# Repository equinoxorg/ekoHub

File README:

Hardware:
Contains all PCB designs and hardware related stuff

Other Folders will come soon

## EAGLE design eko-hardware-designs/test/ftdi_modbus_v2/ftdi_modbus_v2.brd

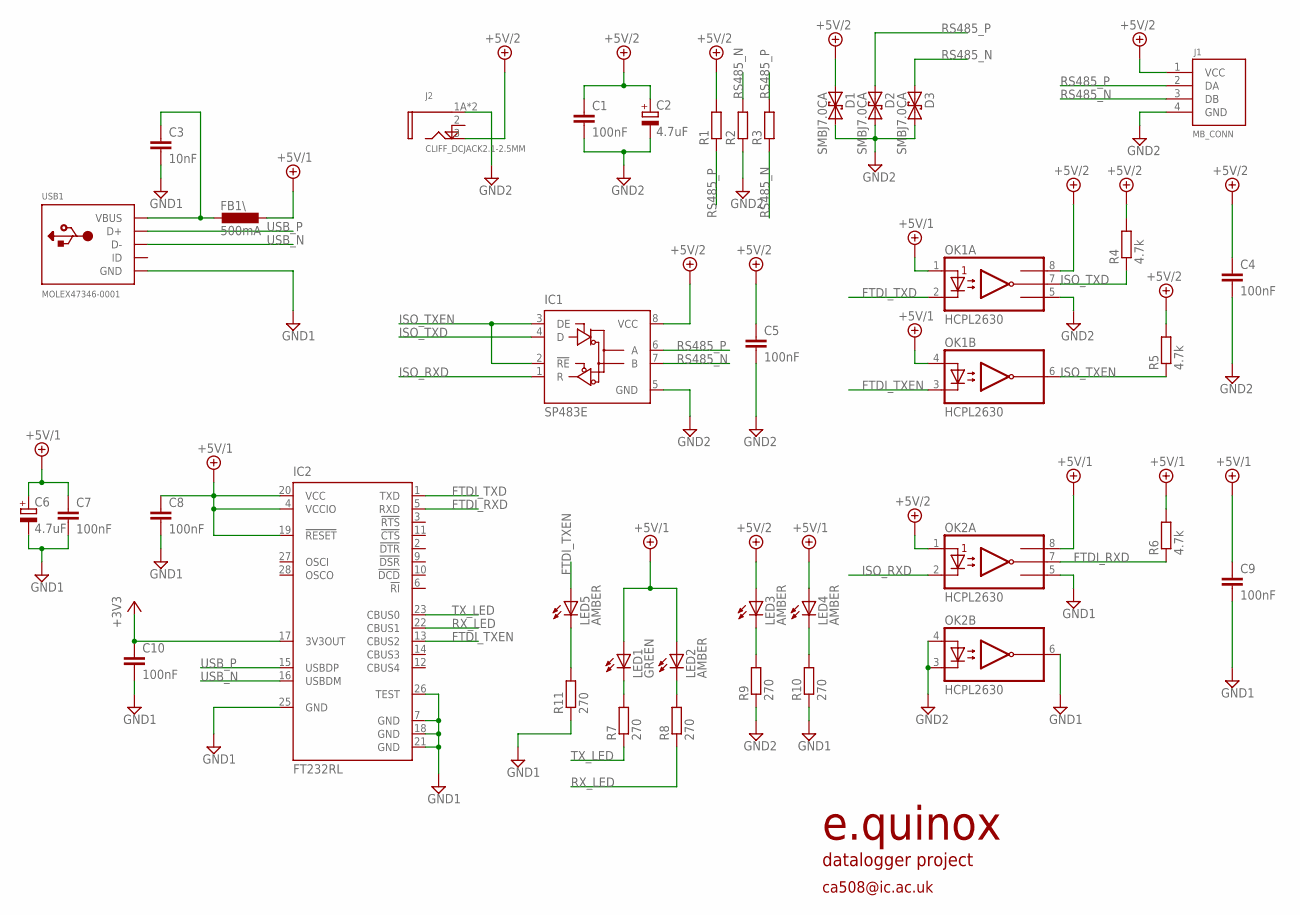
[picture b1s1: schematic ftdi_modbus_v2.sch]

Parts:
C1, C5, C7, C8, C10: 100nF; C0603
C2, C6: 4.7uF; B/3528-21R
C3: 10nF; C0603
C4, C9: 100nF; C1206
D1, D2, D3: SMBJ7.0CA; DO214AA
FB1\: 500mA; L3216C
IC1: SP483E; D_R-PDSO-G8
IC2: FT232RL; SSOP28
J1: MB_CONN; PTSM0,5/4-HH-2,5-THR
J2: CLIFF_DCJACK2.1-2.5MM; FC6814XS
LED1: GREEN; CHIPLED_0805
LED2, LED3, LED4, LED5: AMBER; CHIPLED_0805
OK1, OK2: HCPL2630; DIL08
R1, R2, R3: R-EU_0207/10; 0207/10
R4, R5, R6: 4.7k; M0805
R7, R8, R9, R10, R11: 270; M0805
USB1: MOLEX47346-0001; 47346-0001

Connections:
+3V3: C10.1, IC2.17 (3V3OUT)
+5V/1: C6.+, C7.1, C8.1, C9.1, FB1\.1, IC2.4 (VCCIO), IC2.19 (!RESET), IC2.20 (VCC), LED1.A, LED2.A, LED4.A, OK1.1 (A1), OK1.4 (A2), OK2.8 (VCC), R6.2
+5V/2: C1.1, C2.+, C4.1, C5.1, D1.P$1 (1), IC1.8 (VCC), J1.1 (VCC), J2.3 (TIP), LED3.A, OK1.8 (VCC), OK2.1 (A1), R1.2, R4.2, R5.2
FTDI_RXD: IC2.5 (RXD), OK2.7 (VO1), R6.1
FTDI_TXD: IC2.1 (TXD), OK1.2 (C1)
FTDI_TXEN: IC2.13 (CBUS2), LED5.A, OK1.3 (C2)
GND1: C3.2, C6.-, C7.2, C8.2, C9.2, C10.2, IC2.7 (GND), IC2.18 (GND), IC2.21 (GND), IC2.25 (GND), IC2.26 (TEST), OK2.5 (GND), OK2.6 (VO2), R10.1, R11.1, USB1.5 (GND)
GND2: C1.2, C2.-, C4.2, C5.2, D1.P$2 (2), D2.P$2 (2), D3.P$2 (2), IC1.5 (GND), J1.4 (GND), J2.1A (SLEEVE), J2.1B (SLEEVE), OK1.5 (GND), OK2.3 (C2), OK2.4 (A2), R2.1, R9.1
ISO_RXD: IC1.1 (R), OK2.2 (C1)
ISO_TXD: IC1.4 (D), OK1.7 (VO1), R4.1
ISO_TXEN: IC1.2 (!RE), IC1.3 (DE), OK1.6 (VO2), R5.1
unnamed: C3.1, FB1\.2, USB1.1 (VBUS)
unnamed: LED1.C, R7.2
unnamed: LED2.C, R8.2
unnamed: LED3.C, R9.2
unnamed: LED4.C, R10.2
unnamed: LED5.C, R11.2
RS485_N: D3.P$1 (1), IC1.7 (B), J1.3 (DB), R2.2, R3.1
RS485_P: D2.P$1 (1), IC1.6 (A), J1.2 (DA), R1.1, R3.2
RX_LED: IC2.22 (CBUS1), R8.1
SHUNT: J2.2 (SHUNT)
TX_LED: IC2.23 (CBUS0), R7.1
USB_N: IC2.16 (USBDM), USB1.2 (D-)
USB_P: IC2.15 (USBDP), USB1.3 (D+)

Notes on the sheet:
ca508@ic.ac.uk
e.quinox
datalogger project

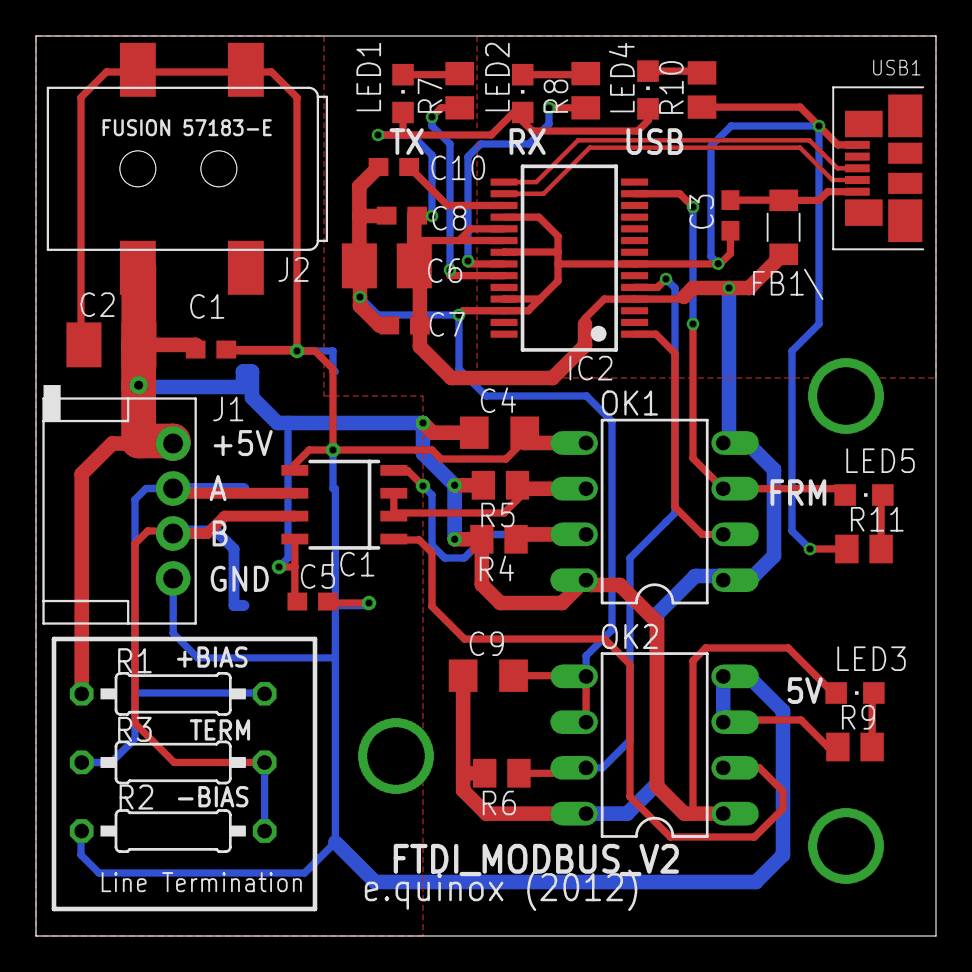
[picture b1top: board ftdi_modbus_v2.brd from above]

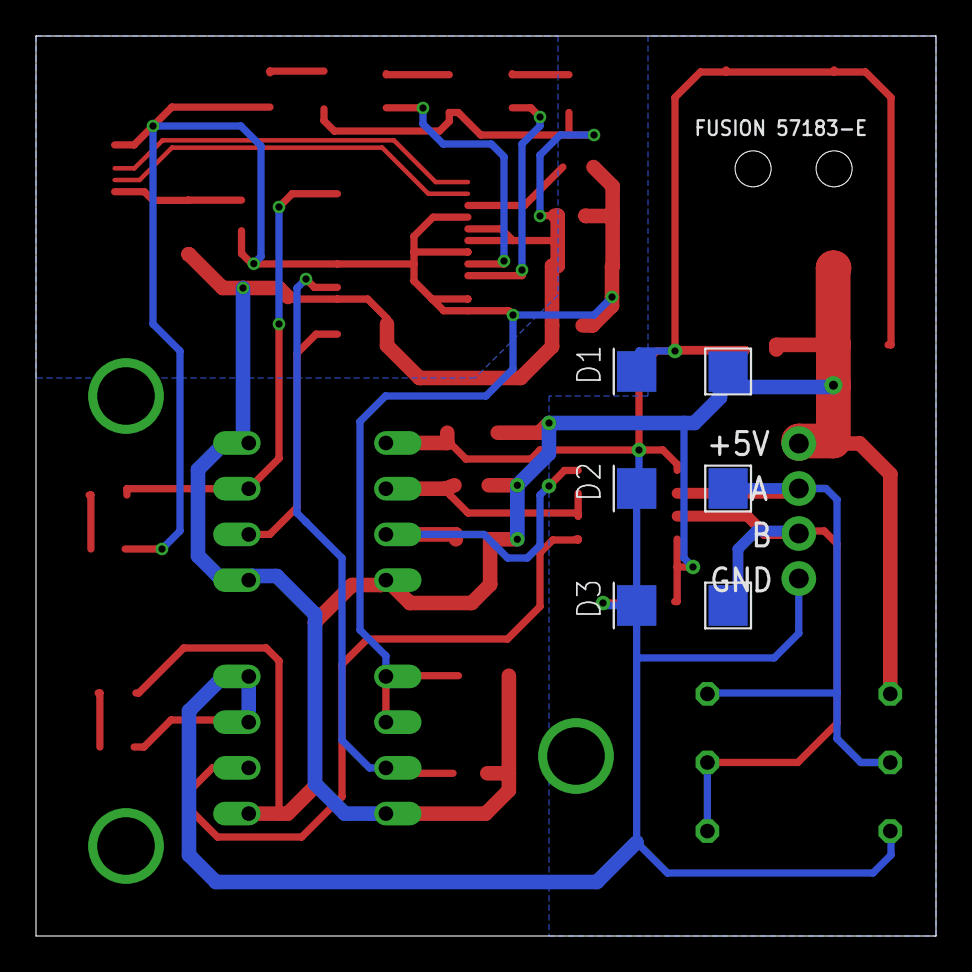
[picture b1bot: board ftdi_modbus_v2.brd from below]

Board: 2 copper layers, 50.0 x 50.0 mm, 37 parts (3 on the bottom side), 23 nets.

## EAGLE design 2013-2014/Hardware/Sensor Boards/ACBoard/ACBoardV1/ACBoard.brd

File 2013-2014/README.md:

Datalogging_2013-2014
=====================

Files for the Datalogging Project 2013-2014

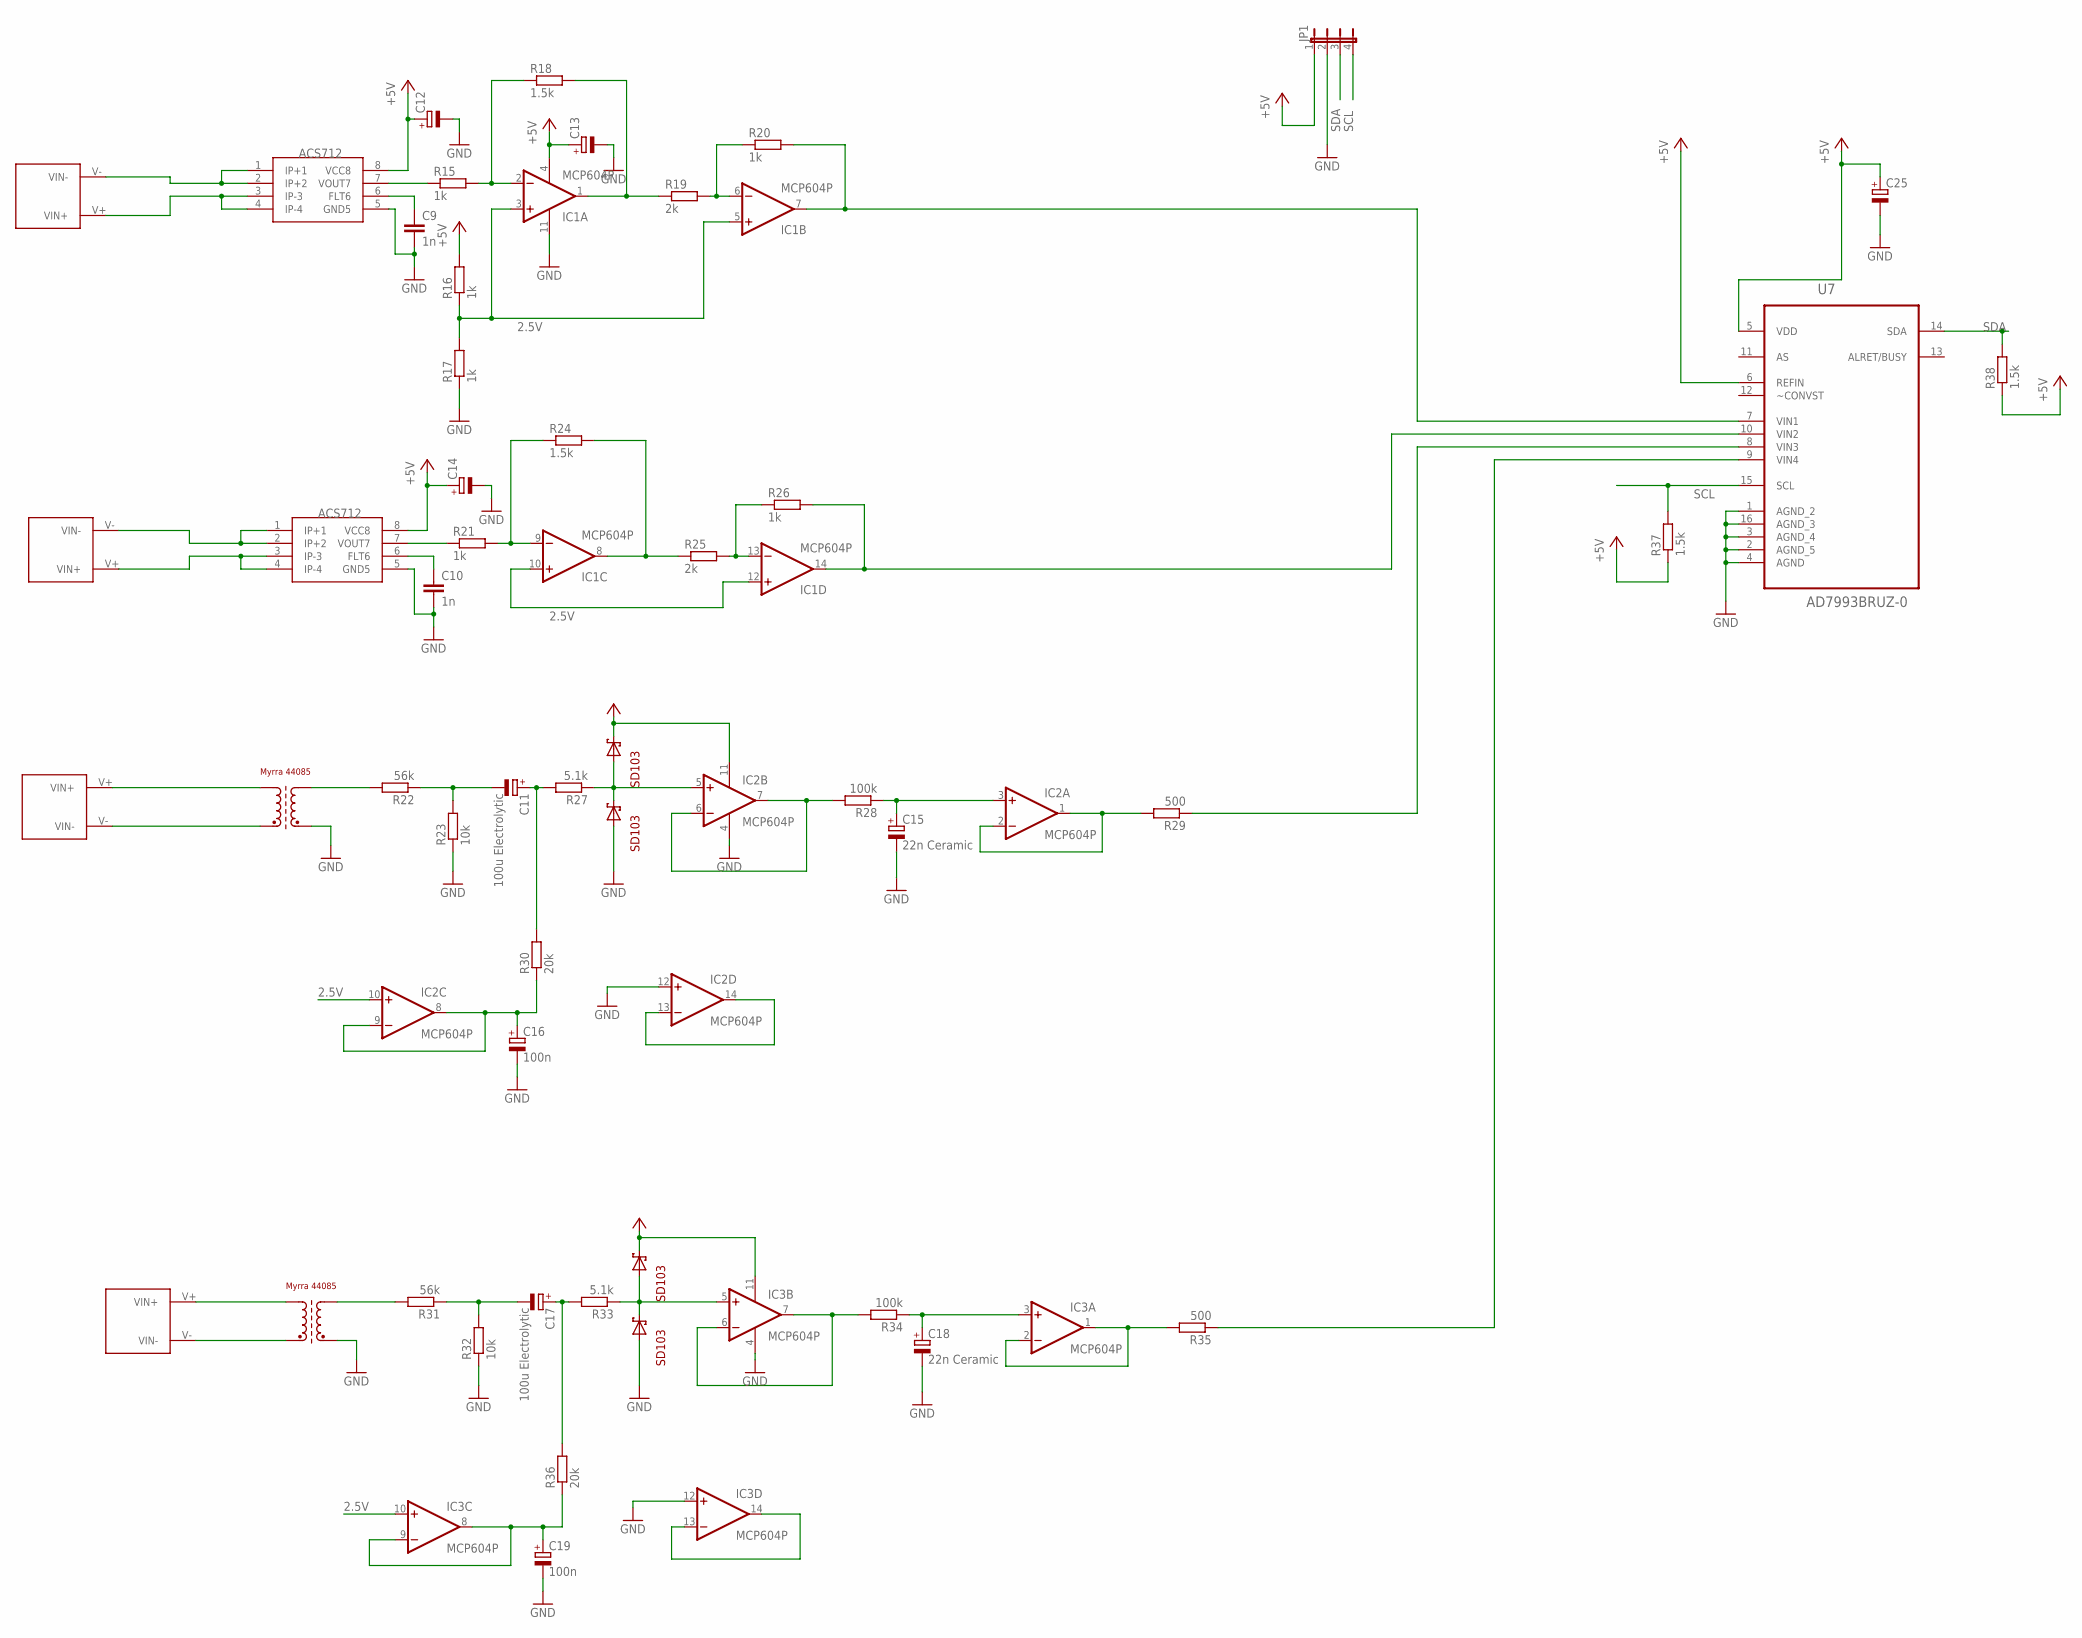
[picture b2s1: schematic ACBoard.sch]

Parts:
C9, C10: 1n; C050-050X075
C11, C17: 100u Electrolytic; E2,5-7---100UF
C12, C13, C14: CPOL1; E2,5-7---100UF
C15, C18: 22n Ceramic; E2,5-7---100UF
C16, C19: 100n; E2,5-7---100UF
C25: CPOL-EUE2-4; E2-4
IC1, IC2, IC3: MCP604P; DIL14
JP1: JP4E; JP4
R15, R16, R17, R20, R21, R26: 1k; 0309/12
R18, R24, R37, R38: 1.5k; 0309/12
R19, R25: 2k; 0309/12
R22, R31: 56k; 0207/10
R23, R32: 10k; 0207/10
R27, R33: 5.1k; 0207/10
R28, R34: 100k; 0207/10
R29, R35: 500; 0207/10
R30, R36: 20k; 0207/10
U7: AD7993BRUZ-0; SOP65P640X120-16N
U$1, U$2, U$3, U$4: INPUT_VOLTAGE_CONNECTOR
U$9, U$11: ACS712; SOIC8
U$14, U$18: MYRRA_4408; 4408
U$15, U$16, U$19, U$20: SD103A; D035-10

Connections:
2.5V: IC1.3 (+IN), IC1.5 (+IN), IC1.10 (+IN), IC1.12 (+IN), IC2.10 (+IN), IC3.10 (+IN), R16.1, R17.2
+3V3: IC2.11 (V-), IC3.11 (V-), U$15.C, U$19.C
+5V: C12.+, C13.+, C14.+, C25.+, IC1.4 (V+), JP1.1, R16.2, R37.1, R38.1, U7.5 (VDD), U7.6 (REFIN), U$9.8 (VCC8), U$11.8 (VCC8)
GND: C9.2, C10.2, C12.-, C13.-, C14.-, C15.-, C16.-, C18.-, C19.-, C25.-, IC1.11 (V-), IC2.4 (V+), IC2.12 (+IN), IC3.4 (V+), IC3.12 (+IN), JP1.2, R17.1, R23.1, R32.1, U7.1 (AGND_2), U7.2 (AGND_5), U7.3 (AGND_4), U7.4 (AGND), U7.16 (AGND_3), U$9.5 (GND5), U$11.5 (GND5), U$14.PIN9 (E2), U$16.A, U$18.PIN9 (E2), U$20.A
I_OUT1: R29.1, U7.8 (VIN3)
I_OUT2: R35.1, U7.9 (VIN4)
unnamed: U$3.V+ (VIN+), U$9.3 (IP-3), U$9.4 (IP-4)
unnamed: U$3.V- (VIN-), U$9.1 (IP+1), U$9.2 (IP+2)
unnamed: R15.1, U$9.7 (VOUT7)
unnamed: IC1.2 (-IN), R15.2, R18.1
unnamed: C9.1, U$9.6 (FLT6)
unnamed: U$1.V+ (VIN+), U$14.PIN5 (A1)
unnamed: IC1.6 (-IN), R19.2, R20.1
unnamed: IC1.1 (OUT), R18.2, R19.1
unnamed: U$2.V+ (VIN+), U$11.3 (IP-3), U$11.4 (IP-4)
unnamed: U$2.V- (VIN-), U$11.1 (IP+1), U$11.2 (IP+2)
unnamed: R21.1, U$11.7 (VOUT7)
unnamed: IC1.9 (-IN), R21.2, R24.1
unnamed: C10.1, U$11.6 (FLT6)
unnamed: U$1.V- (VIN-), U$14.PIN1 (E1)
unnamed: IC1.8 (OUT), R24.2, R25.1
unnamed: IC1.13 (-IN), R25.2, R26.1
unnamed: R22.2, U$14.PIN7 (A2)
unnamed: C11.-, R22.1, R23.2
unnamed: C11.+, R27.2, R30.2
unnamed: IC2.5 (+IN), R27.1, U$15.A, U$16.C
unnamed: IC2.6 (-IN), IC2.7 (OUT), R28.2
unnamed: C15.+, IC2.3 (+IN), R28.1
unnamed: IC2.1 (OUT), IC2.2 (-IN), R29.2
unnamed: C16.+, IC2.8 (OUT), IC2.9 (-IN), R30.1
unnamed: IC2.13 (-IN), IC2.14 (OUT)
unnamed: U$4.V+ (VIN+), U$18.PIN5 (A1)
unnamed: U$4.V- (VIN-), U$18.PIN1 (E1)
unnamed: R31.2, U$18.PIN7 (A2)
unnamed: C17.-, R31.1, R32.2
unnamed: C17.+, R33.2, R36.2
unnamed: IC3.5 (+IN), R33.1, U$19.A, U$20.C
unnamed: IC3.6 (-IN), IC3.7 (OUT), R34.2
unnamed: C18.+, IC3.3 (+IN), R34.1
unnamed: IC3.1 (OUT), IC3.2 (-IN), R35.2
unnamed: C19.+, IC3.8 (OUT), IC3.9 (-IN), R36.1
unnamed: IC3.13 (-IN), IC3.14 (OUT)
SCL: JP1.4, R37.2, U7.15 (SCL)
SDA: JP1.3, R38.2, U7.14 (SDA)
VAC_OUT1: IC1.7 (OUT), R20.2, U7.7 (VIN1)
VAC_OUT2: IC1.14 (OUT), R26.2, U7.10 (VIN2)

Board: 2 copper layers, 57 parts (0 on the bottom side), 46 nets, no tracks yet.

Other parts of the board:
U$5, U$6, U$7, U$8: 3,0

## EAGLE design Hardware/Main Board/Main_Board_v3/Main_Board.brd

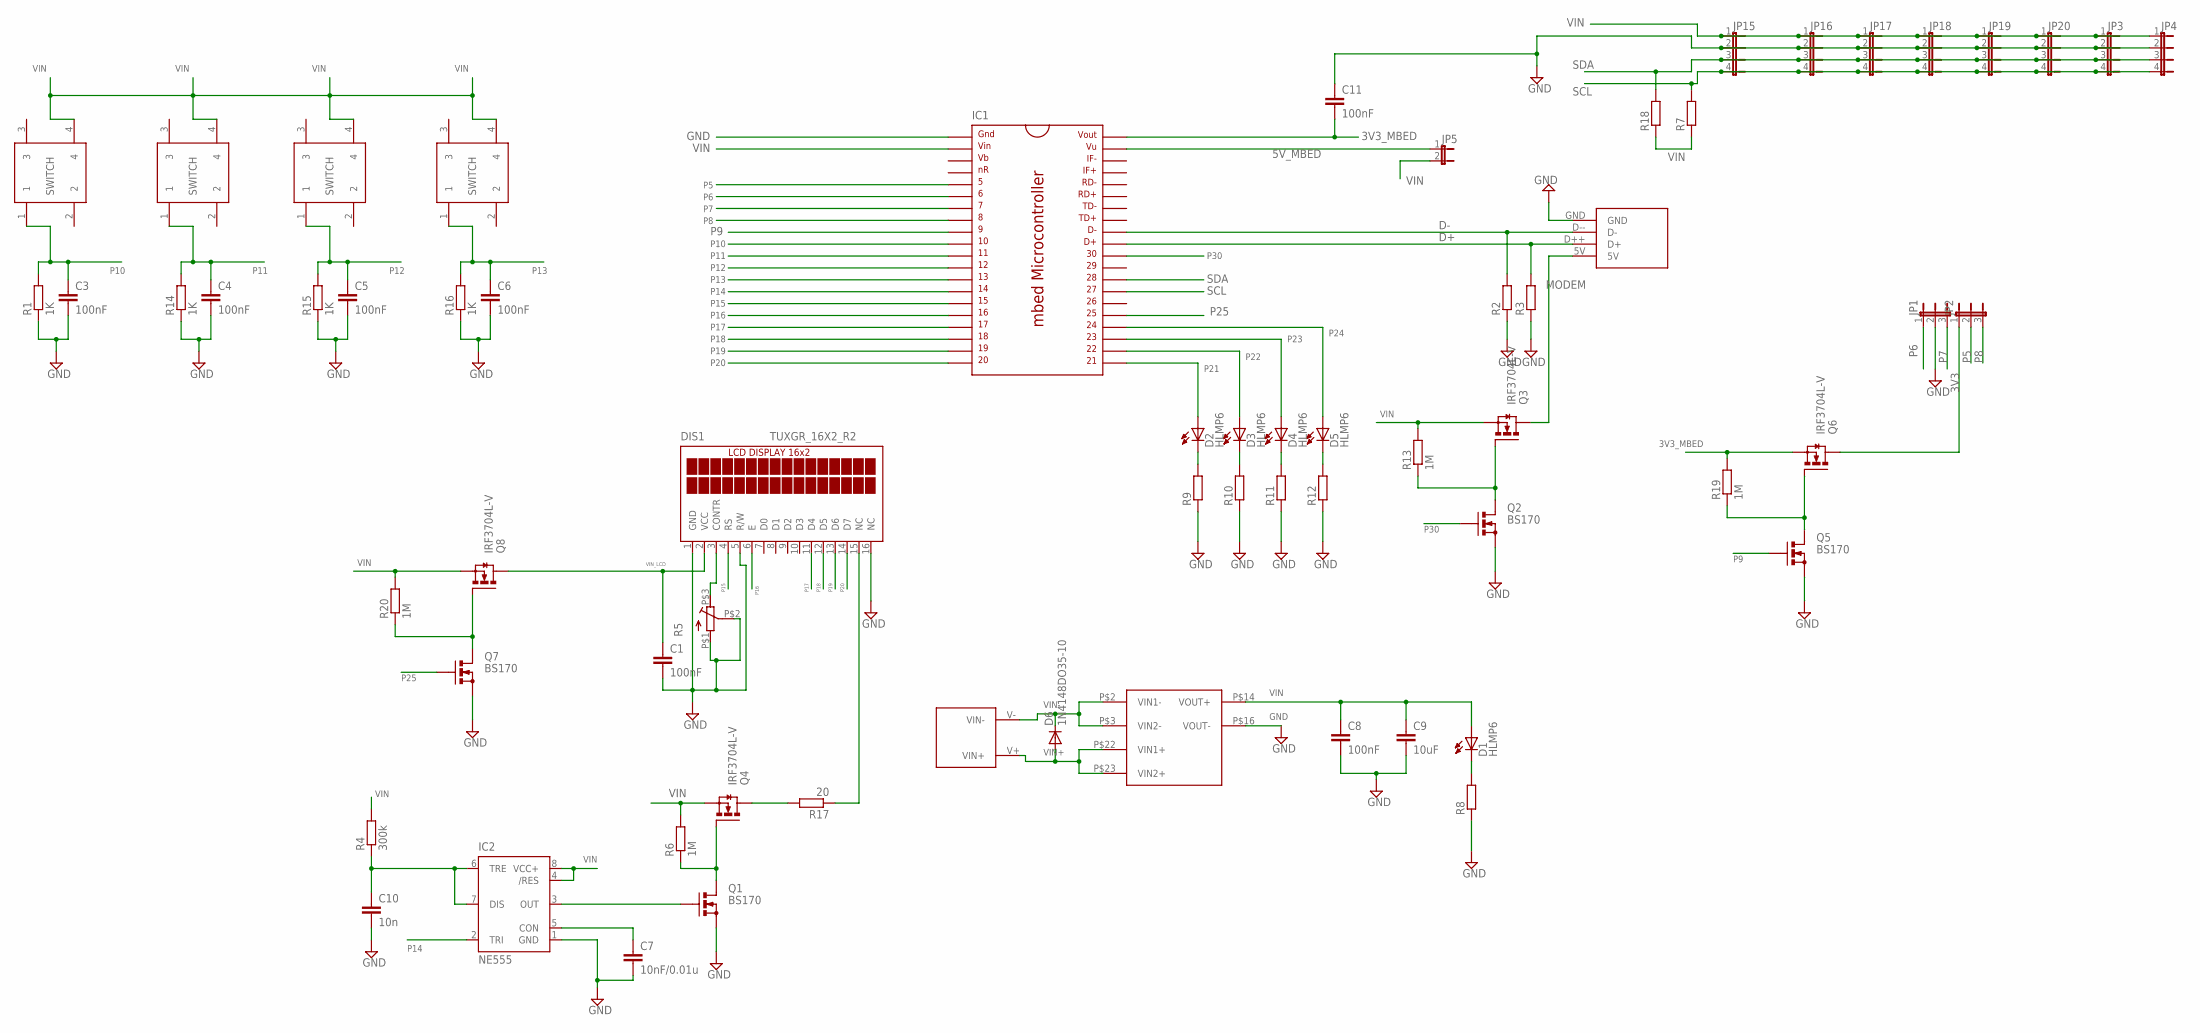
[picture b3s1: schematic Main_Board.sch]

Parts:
C1, C3, C4, C5, C6, C8, C11: 100nF; C5B3.5
C7: 10nF/0.01u; C5B3.5
C9: 10uF; C5B3.5
C10: 10n; C5B3.5
D1, D2, D3, D4, D5: HLMP6
D6: 1N4148DO35-10; DO35-10
DIS1: TUXGR_16X2_R2
IC1: MBED_MICROCONTROLLER; DIL40_0.9
IC2: NE555; DIL-08
JP1, JP2: JP2W
JP3, JP4, JP15, JP16, JP17, JP18, JP19, JP20: JP4E; JP4
JP5: JP1E; JP1
Q1, Q2, Q5, Q7: BS170; SOT54E
Q3, Q4, Q6, Q8: IRF3704L-V; TO262-V
R1, R14, R15, R16: 1K; 0411/12
R2, R3, R7, R8, R9, R10, R11, R12, R18: R-EU_0411/12; 0411/12
R4: 300k; 0411/12
R5: R-TRIMM; IRG2014TRIM
R6, R13, R19, R20: 1M; 0411/12
R17: 20; 0411/12
U$1: USBA_SOCKET
U$4: INPUT_VOLTAGE_CONNECTOR
U$5, U$6, U$7, U$8: TACT_SWITCH
U$9: TRACO_ISOLATED_SUPPLY

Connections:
3V3: JP2.1, Q6.2 (D)
3V3_MBED: C11.2, IC1.40, Q6.3 (S), R19.2
5V_MBED: IC1.39, JP5.1
D+: IC1.31, R3.2, U$1.D++ (D+)
D-: IC1.32, R2.2, U$1.D-- (D-)
GND: C1.2, C3.2, C4.2, C5.2, C6.2, C7.2, C8.2, C9.2, C10.2, C11.1, DIS1.1 (GND), DIS1.5 (R/W), DIS1.16 (NC), IC1.1, IC2.1 (GND), JP1.2, JP3.2, JP4.2, JP15.2, JP16.2, JP17.2, JP18.2, JP19.2, JP20.2, Q1.S, Q2.S, Q5.S, Q7.S, R1.1, R2.1, R3.1, R5.P$1 (A), R5.P$2 (S), R8.1, R9.1, R10.1, R11.1, R12.1, R14.1, R15.1, R16.1, U$1.GND, U$9.P$16 (VOUT-)
MODEM: Q3.2 (D), U$1.5V
unnamed: D1.K, R8.2
unnamed: C7.1, IC2.5 (CON)
unnamed: DIS1.3 (CONTR), R5.P$3 (E)
unnamed: D2.K, R9.2
unnamed: Q2.D, Q3.1 (G), R13.1
unnamed: C10.1, IC2.6 (TRE), IC2.7 (DIS), R4.1
unnamed: Q5.D, Q6.1 (G), R19.1
unnamed: Q1.D, Q4.1 (G), R6.1
unnamed: DIS1.15 (NC), R17.1
unnamed: Q7.D, Q8.1 (G), R20.1
unnamed: IC2.3 (OUT), Q1.G
unnamed: Q4.2 (D), R17.2
unnamed: D3.K, R10.2
unnamed: D4.K, R11.2
unnamed: D5.K, R12.2
P5: IC1.5, JP2.2
P6: IC1.6, JP1.1
P7: IC1.7, JP1.3
P8: IC1.8, JP2.3
P9: IC1.9, Q5.G
P10: C3.1, IC1.10, R1.2, U$5.1
P11: C4.1, IC1.11, R14.2, U$6.1
P12: C5.1, IC1.12, R15.2, U$7.1
P13: C6.1, IC1.13, R16.2, U$8.1
P14: IC1.14, IC2.2 (TRI)
P15: DIS1.4 (RS), IC1.15
P16: DIS1.6 (E), IC1.16
P17: DIS1.11 (D4), IC1.17
P18: DIS1.12 (D5), IC1.18
P19: DIS1.13 (D6), IC1.19
P20: DIS1.14 (D7), IC1.20
P21: D2.A, IC1.21
P22: D3.A, IC1.22
P23: D4.A, IC1.23
P24: D5.A, IC1.24
P25: IC1.25, Q7.G
P30: IC1.30, Q2.G
SCL: IC1.27, JP3.4, JP4.4, JP15.4, JP16.4, JP17.4, JP18.4, JP19.4, JP20.4, R7.2
SDA: IC1.28, JP3.3, JP4.3, JP15.3, JP16.3, JP17.3, JP18.3, JP19.3, JP20.3, R18.2
VIN: C8.1, C9.1, D1.A, IC1.2, IC2.4 (/RES), IC2.8 (VCC+), JP3.1, JP4.1, JP5.2, JP15.1, JP16.1, JP17.1, JP18.1, JP19.1, JP20.1, Q3.3 (S), Q4.3 (S), Q8.3 (S), R4.2, R6.2, R7.1, R13.2, R18.1, R20.2, U$5.4, U$6.4, U$7.4, U$8.4, U$9.P$14 (VOUT+)
VIN+: D6.A, U$4.V+ (VIN+), U$9.P$22 (VIN1+), U$9.P$23 (VIN2+)
VIN-: D6.C, U$4.V- (VIN-), U$9.P$2 (VIN1-), U$9.P$3 (VIN2-)
VIN_LCD: C1.1, DIS1.2 (VCC), Q8.2 (D)

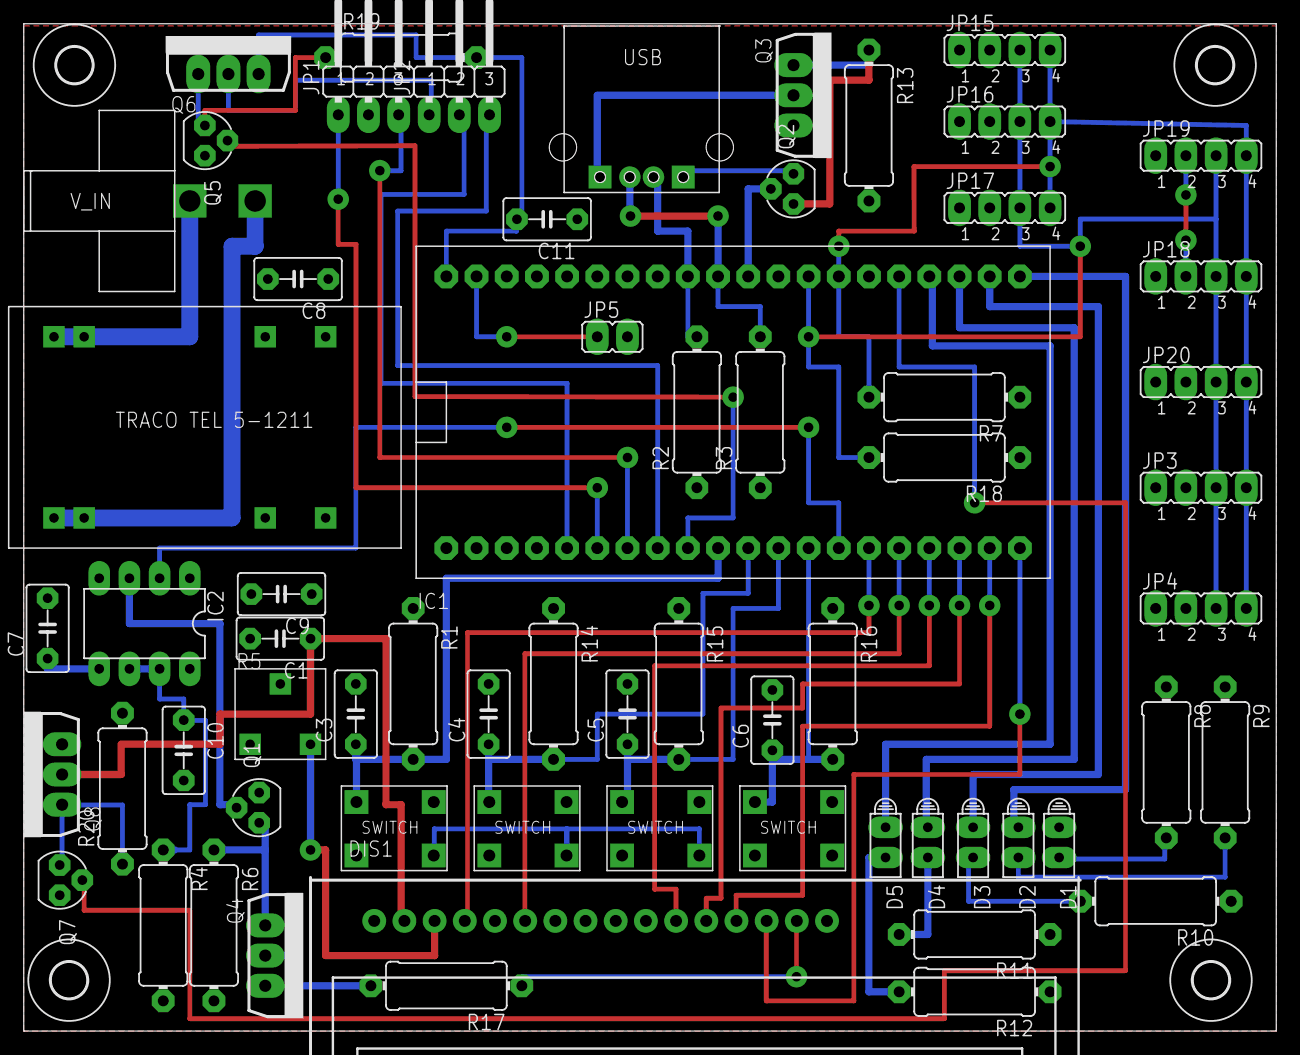
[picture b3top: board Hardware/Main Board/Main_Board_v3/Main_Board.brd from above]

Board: 2 copper layers, 105.4 x 84.8 mm, 68 parts (0 on the bottom side), 50 nets.

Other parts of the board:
U$10, U$11, U$12, U$13: 3,0

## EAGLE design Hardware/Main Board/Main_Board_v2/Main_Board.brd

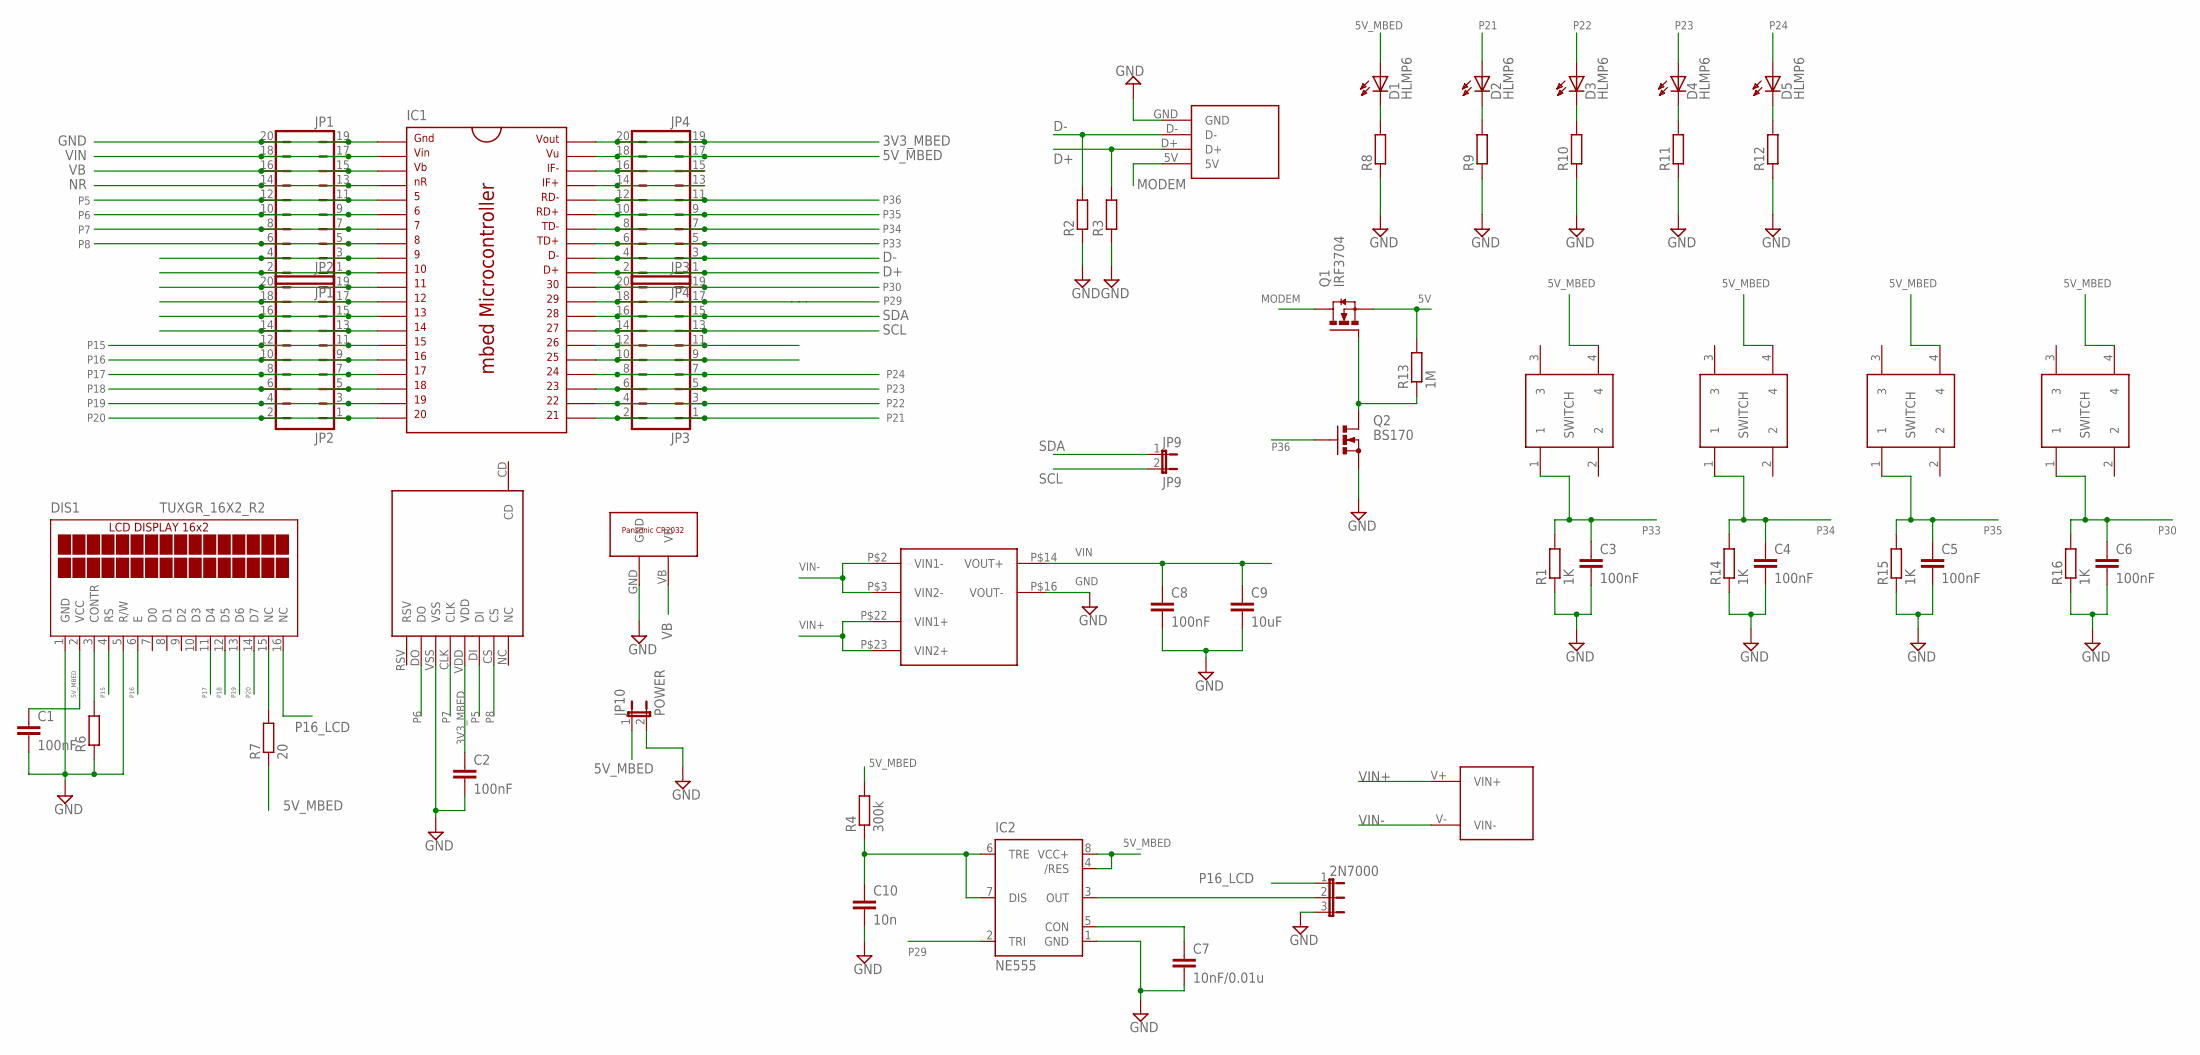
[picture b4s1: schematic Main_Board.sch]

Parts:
2N7000: JP2E; JP2
C1, C2, C3, C4, C5, C6, C8: 100nF; C5B3
C7: 10nF/0.01u; C5B3
C9: 10uF; C5B3
C10: 10n; C5B3
D1, D2, D3, D4, D5: HLMP6
DIS1: TUXGR_16X2_R2
IC1: MBED_MICROCONTROLLER; DIL40_0.9
IC2: NE555; DIL-08
JP1: JP1; JP10Q
JP2: JP2; JP10Q
JP3: JP3; JP10Q
JP4: JP4; JP10Q
JP9: JP9; JP1
JP10: POWER; JP1
Q1: IRF3704; TO220AH
Q2: BS170; SOT54E
R1, R14, R15, R16: 1K; 0411/12
R2, R3, R6, R8, R9, R10, R11, R12: R-EU_0411/12; 0411/12
R4: 300k; 0411/12
R7: 20; 0411/12
R13: 1M; 0411/12
U$1: USBA_SOCKET
U$2: MICROSD_SOCKET
U$3: PANASONIC_CR2032
U$4: INPUT_VOLTAGE_CONNECTOR
U$5, U$6, U$7, U$8: TACT_SWITCH
U$9: TRACO_ISOLATED_SUPPLY

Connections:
3V3_MBED: C2.1, IC1.40, JP4.19, JP4.20, U$2.VDD
5V: Q1.E (S), R13.2; also elsewhere on the board
5V_MBED: C1.1, D1.A, DIS1.2 (VCC), IC1.39, IC2.4 (/RES), IC2.8 (VCC+), JP4.17, JP4.18, JP10.1, R4.2, R7.1, U$5.4, U$6.4, U$7.4, U$8.4
D+: IC1.31, JP4.1, JP4.2, R3.2, U$1.D+, U$1.D++
D-: IC1.32, JP4.3, JP4.4, R2.2, U$1.D-, U$1.D--
GND: 2N7000.3, C1.2, C2.2, C3.2, C4.2, C5.2, C6.2, C7.2, C8.2, C9.2, C10.2, DIS1.1 (GND), DIS1.5 (R/W), IC1.1, IC2.1 (GND), JP1.19, JP1.20, JP10.2, Q2.S, R1.1, R2.1, R3.1, R6.1, R8.1, R9.1, R10.1, R11.1, R12.1, R14.1, R15.1, R16.1, U$1.GND, U$2.VSS, U$3.GND, U$9.P$16 (VOUT-)
MODEM: Q1.C (D), U$1.5V; also elsewhere on the board
unnamed: D1.K, R8.2
unnamed: C7.1, IC2.5 (CON)
unnamed: DIS1.3 (CONTR), R6.2
unnamed: D2.K, R9.2
unnamed 11: Q1.B (G), Q2.D, R13.1; also elsewhere on the board
unnamed: C10.1, IC2.6 (TRE), IC2.7 (DIS), R4.1
unnamed: 2N7000.2, IC2.3 (OUT)
unnamed: IC1.9, JP1.3, JP1.4
unnamed: IC1.10, JP1.1, JP1.2
unnamed: IC1.11, JP2.19, JP2.20
unnamed: IC1.12, JP2.17, JP2.18
unnamed: IC1.13, JP2.15, JP2.16
unnamed: IC1.14, JP2.13, JP2.14
unnamed: D3.K, R10.2
unnamed: D4.K, R11.2
unnamed: D5.K, R12.2
unnamed: IC1.38, JP4.15, JP4.16
unnamed: IC1.37, JP4.13, JP4.14
unnamed: IC1.26, JP3.11, JP3.12
unnamed: IC1.25, JP3.9, JP3.10
unnamed: DIS1.15 (NC), R7.2
NR: IC1.4, JP1.13, JP1.14
P5: IC1.5, JP1.11, JP1.12, U$2.DI
P6: IC1.6, JP1.9, JP1.10, U$2.DO
P7: IC1.7, JP1.7, JP1.8, U$2.CLK
P8: IC1.8, JP1.5, JP1.6, U$2.CS
P15: DIS1.4 (RS), IC1.15, JP2.11, JP2.12
P16: DIS1.6 (E), IC1.16, JP2.9, JP2.10
P16_LCD: 2N7000.1, DIS1.16 (NC)
P17: DIS1.11 (D4), IC1.17, JP2.7, JP2.8
P18: DIS1.12 (D5), IC1.18, JP2.5, JP2.6
P19: DIS1.13 (D6), IC1.19, JP2.3, JP2.4
P20: DIS1.14 (D7), IC1.20, JP2.1, JP2.2
P21: D2.A, IC1.21, JP3.1, JP3.2
P22: D3.A, IC1.22, JP3.3, JP3.4
P23: D4.A, IC1.23, JP3.5, JP3.6
P24: D5.A, IC1.24, JP3.7, JP3.8
P29: IC1.29, IC2.2 (TRI), JP3.17, JP3.18
P30: C6.1, IC1.30, JP3.19, JP3.20, R16.2, U$8.1
P33: C3.1, IC1.33, JP4.5, JP4.6, R1.2, U$5.1
P34: C4.1, IC1.34, JP4.7, JP4.8, R14.2, U$6.1
P35: C5.1, IC1.35, JP4.9, JP4.10, R15.2, U$7.1
P36: IC1.36, JP4.11, JP4.12, Q2.G
SCL: IC1.27, JP3.13, JP3.14, JP9.2
SDA: IC1.28, JP3.15, JP3.16, JP9.1
VB: IC1.3, JP1.15, JP1.16, U$3.VB
VIN: C8.1, C9.1, IC1.2, JP1.17, JP1.18, U$9.P$14 (VOUT+)
VIN+: U$4.V+ (VIN+), U$9.P$22 (VIN1+), U$9.P$23 (VIN2+)
VIN-: U$4.V- (VIN-), U$9.P$2 (VIN1-), U$9.P$3 (VIN2-)

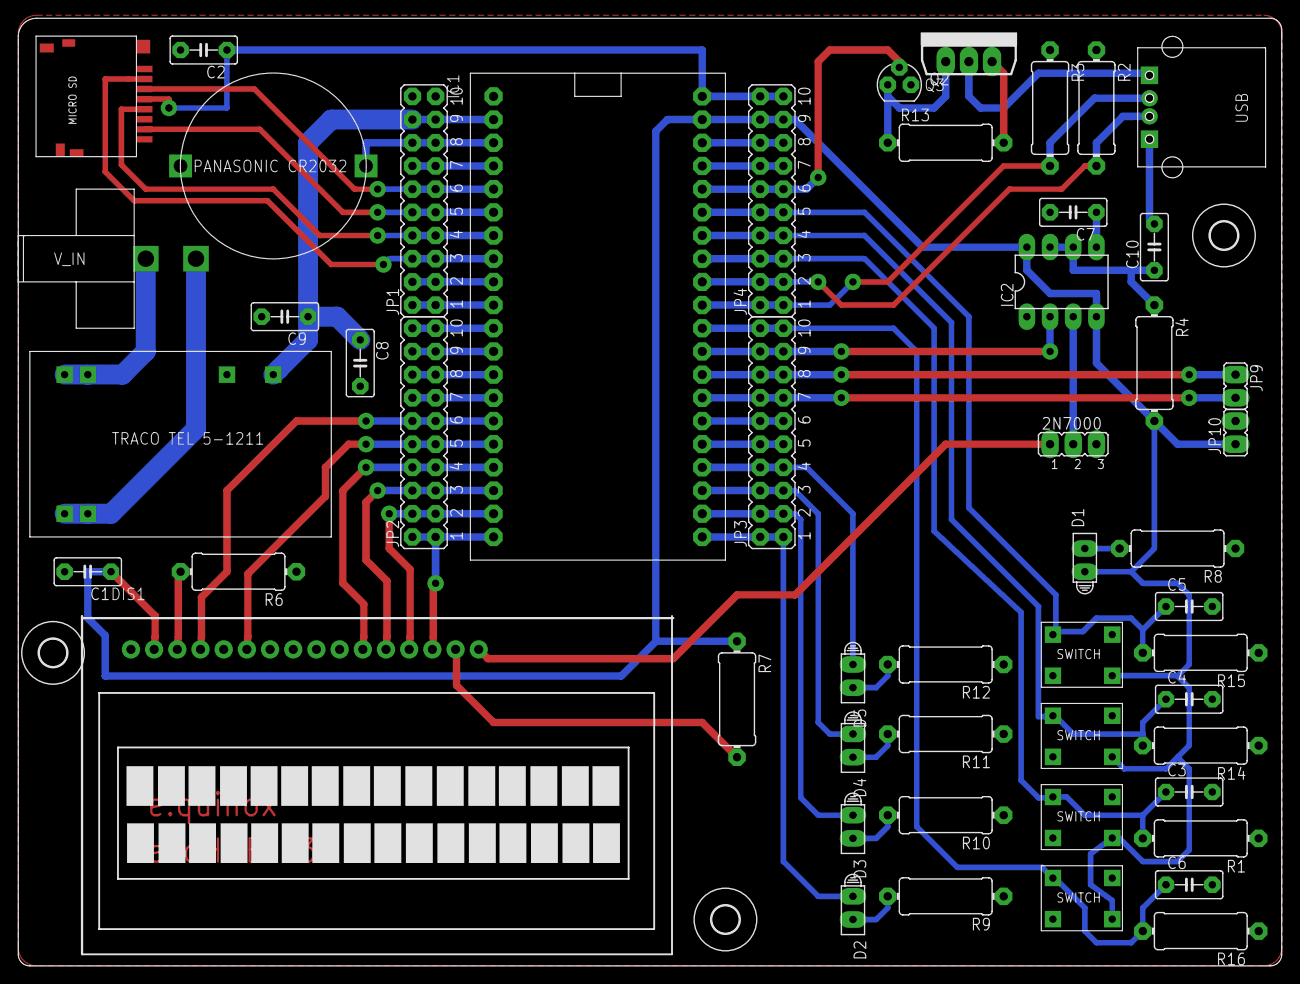
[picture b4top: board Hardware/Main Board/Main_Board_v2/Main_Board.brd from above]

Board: 2 copper layers, 138.4 x 103.8 mm, 54 parts (0 on the bottom side), 56 nets.

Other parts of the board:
Q3: IRF3704L-V; TO262-V
U$10, U$11, U$12: 3,0

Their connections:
5V: Q3.3; also elsewhere on the board
MODEM: Q3.2; also elsewhere on the board
unnamed 11: Q3.1; also elsewhere on the board

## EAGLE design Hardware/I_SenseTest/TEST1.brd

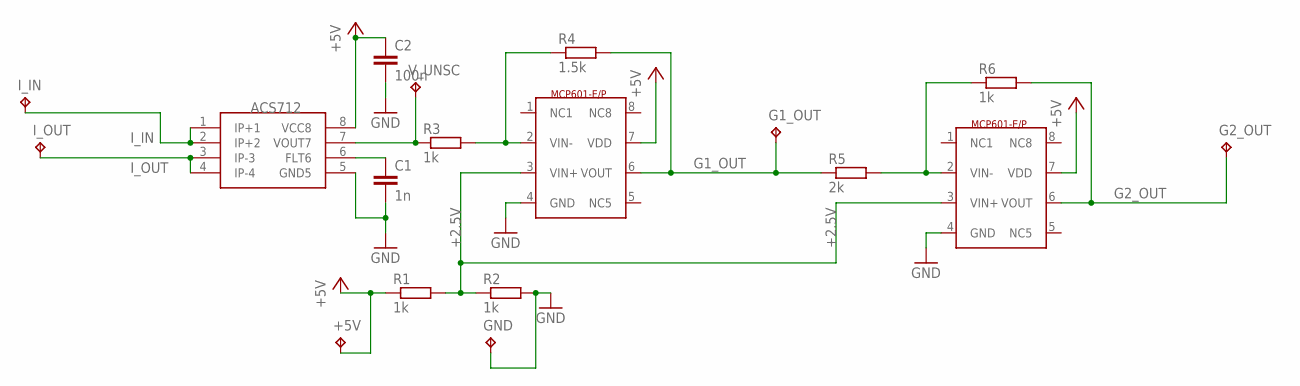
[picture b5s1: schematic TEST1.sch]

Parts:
+5V: TPPAD1-17Y; P1-17Y
C1: 1n; C050-050X075
C2: 100n; C050-050X075
G1_OUT, G2_OUT: TPPAD1-17Y; P1-17Y
GND: TPPAD1-17Y; P1-17Y
I_IN: TPPAD1-17Y; P1-17Y
I_OUT: TPPAD1-17Y; P1-17Y
R1, R2, R3, R6: 1k; 0309/12
R4: 1.5k; 0309/12
R5: 2k; 0309/12
U$1: ACS712; SOIC8
U$2, U$3: MCP601; PDIP8
V_UNSC: TPPAD1-17Y; P1-17Y

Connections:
+2.5V: R1.2, R2.1, U$2.3 (VIN+), U$3.3 (VIN+)
+5V: +5V.TP, C2.1, R1.1, U$1.8 (VCC8), U$2.7 (VDD), U$3.7 (VDD)
G1_OUT: G1_OUT.TP, R4.2, R5.1, U$2.6 (VOUT)
G2_OUT: G2_OUT.TP, R6.2, U$3.6 (VOUT)
GND: C1.2, C2.2, GND.TP, R2.2, U$1.5 (GND5), U$2.4 (GND), U$3.4 (GND)
I_IN: I_IN.TP, U$1.1 (IP+1), U$1.2 (IP+2)
I_OUT: I_OUT.TP, U$1.3 (IP-3), U$1.4 (IP-4)
unnamed: R3.1, U$1.7 (VOUT7), V_UNSC.TP
unnamed: R3.2, R4.1, U$2.2 (VIN-)
unnamed: R5.2, R6.1, U$3.2 (VIN-)
unnamed: C1.1, U$1.6 (FLT6)

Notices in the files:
parts and their libraries:
con-headers-jp: Copyright (C) 2008, Bob Starr
